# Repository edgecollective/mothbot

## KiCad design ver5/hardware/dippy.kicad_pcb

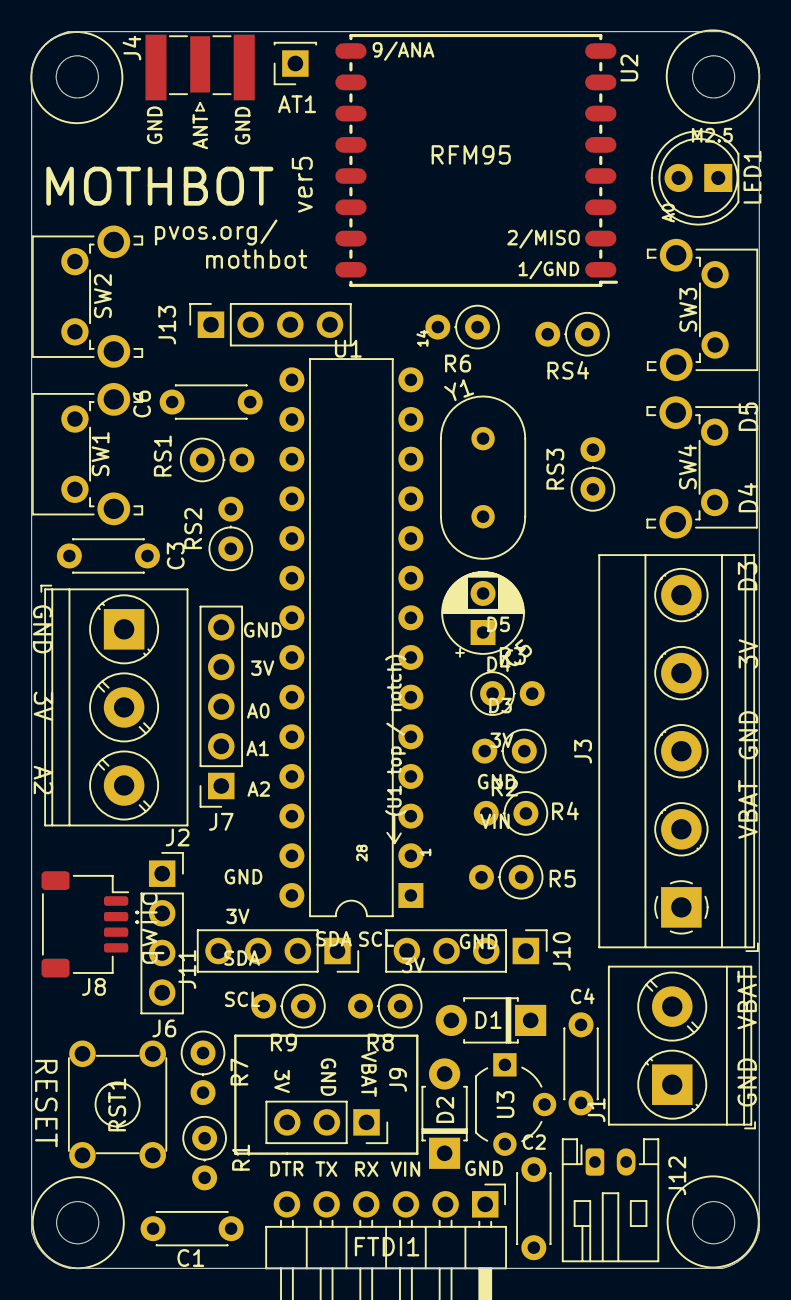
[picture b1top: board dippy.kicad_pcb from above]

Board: 2 copper layers, 46.6 x 79.2 mm, 50 parts (1 on the bottom side), 30 nets, no tracks yet.

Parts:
AT1: Conn_01x01_Female; PinSocket_1x01_P2.54mm_Vertical
C1, C2, C3, C4: 0.1u; C_Disc_D4.3mm_W1.9mm_P5.00mm
C5: 10u; CP_Radial_D5.0mm_P2.50mm
C6: 0.1uF; C_Disc_D4.3mm_W1.9mm_P5.00mm
D1, D2: D; D_T-1_P5.08mm_Horizontal
FTDI1: Conn_01x06_Male; PinHeader_1x06_P2.54mm_Horizontal
H1, H2, H3, H4: MountingHole; MountingHole_2.7mm_M2.5
J1: Screw_Terminal_01x02; TerminalBlock_Phoenix_PT-1,5-2-5.0-H_1x02_P5.00mm_Horizontal
J2: Screw_Terminal_01x03; TerminalBlock_Phoenix_PT-1,5-3-5.0-H_1x03_P5.00mm_Horizontal
J3: Screw_Terminal_01x05; TerminalBlock_Phoenix_MKDS-1,5-5_1x05_P5.00mm_Horizontal
J4: Conn_Coaxial; SMA_Samtec_SMA-J-P-X-ST-EM1_EdgeMount
J5: Conn_02x03_Odd_Even; PinSocket_2x03_P2.54mm_Vertical_SMD
J6, J11, J13: Conn_01x04_Female; PinSocket_1x04_P2.54mm_Vertical
J7: Conn_01x05_Female; PinSocket_1x05_P2.54mm_Vertical
J8: Conn_01x04_Female; JST_SH_SM04B-SRSS-TB_1x04-1MP_P1.00mm_Horizontal
J9: Conn_01x03_Female; PinSocket_1x03_P2.54mm_Vertical
J10: Conn_01x04_Female; PinHeader_1x04_P2.54mm_Vertical
J12: Conn_01x02_Female; JST_PH_S2B-PH-K_1x02_P2.00mm_Horizontal
LED1: LED; LED_D5.0mm
R1, R2, R3, R9: 10K; R_Axial_DIN0207_L6.3mm_D2.5mm_P2.54mm_Vertical
R4, R5: 10M; R_Axial_DIN0207_L6.3mm_D2.5mm_P2.54mm_Vertical
R6: 300R; R_Axial_DIN0207_L6.3mm_D2.5mm_P2.54mm_Vertical
R7, R8: R; R_Axial_DIN0207_L6.3mm_D2.5mm_P2.54mm_Vertical
RS1, RS2, RS3, RS4: R; R_Axial_DIN0207_L6.3mm_D2.5mm_P2.54mm_Vertical
RST1: SW_Push_Dual; SW_TH_Tactile_Omron_B3F-10xx
SW1, SW2, SW3, SW4: SW_Push; SW_Tactile_SPST_Angled_PTS645Vx58-2LFS
U1: ATmega328P-PU-C; DIP-28_W7.62mm
U2: RFM95W-915S2; RFM95
U3: MCP1700-3302E_TO92; TO-92_Wide
Y1: Crystal; Resonator-2Pin_W10.0mm_H5.0mm

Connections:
A0: J2.3, J7.3, LED1.2, R2.2, U1.23
A1: J7.2, RS1.2, SW1.1, U1.24
A2: J7.1, RS2.2, SW2.1, U1.25
A3: C6.1, R4.2, R5.1, RS4.2, SW4.1, U1.26
A4: J6.3, J8.3, J11.4, J13.4, R7.2, U1.27
A5: J6.4, J8.4, J11.3, J13.3, R8.2, U1.28
D2: U1.4, U2.14
D3: J3.4, J10.3, R9.2, U1.5
D4: J3.5, J10.4, R3.2, U1.6
D5: RS3.2, SW3.1, U1.11
D6: U1.12, U2.15
D7: U1.13, U2.6
D8: U1.14, U2.5
GND: C2.2, C3.2, C4.2, C5.2, C6.2, FTDI1.1, J1.1, J2.1, J3.2, J4.2, J5.6, J6.1, J7.5, J8.1, J9.2, J10.1, J11.1, J12.1, J13.1, R5.2, R6.2, RST1.3, RST1.4, SW1.2, SW2.2, SW3.2, SW4.2, U1.8, U1.22, U2.1, U2.8, U2.10, U3.1
MISO: J5.1, U1.18, U2.2
MOSI: J5.4, U1.17, U2.3
unnamed: AT1.1, J4.1, U2.9
unnamed: C1.2, FTDI1.6
unnamed: C2.1, D1.1, D2.1, U3.2
unnamed: C3.1, U1.21
unnamed: LED1.1, R6.1
unnamed: U1.9, Y1.1
unnamed: U1.10, Y1.2
RST: C1.1, J5.5, R1.2, RST1.1, RST1.2, U1.1
RX0: FTDI1.4, U1.2
SCK: J5.3, U1.19, U2.4
TX0: FTDI1.5, U1.3
VBAT: D2.2, J1.2, J3.1, J9.1, J12.2, R4.1
VBUS: D1.2, FTDI1.3
VCC: C4.1, C5.1, J2.2, J3.3, J5.2, J6.2, J7.4, J8.2, J9.3, J10.2, J11.2, J13.2, R1.1, R2.1, R3.1, R7.1, R8.1, R9.1, RS1.1, RS2.1, RS3.1, RS4.1, U1.7, U1.20, U2.13, U3.3

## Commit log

2021-01-16 successful back and forth test
2021-01-17 switched labels for R3 and R6
2021-01-17 cleaning up
